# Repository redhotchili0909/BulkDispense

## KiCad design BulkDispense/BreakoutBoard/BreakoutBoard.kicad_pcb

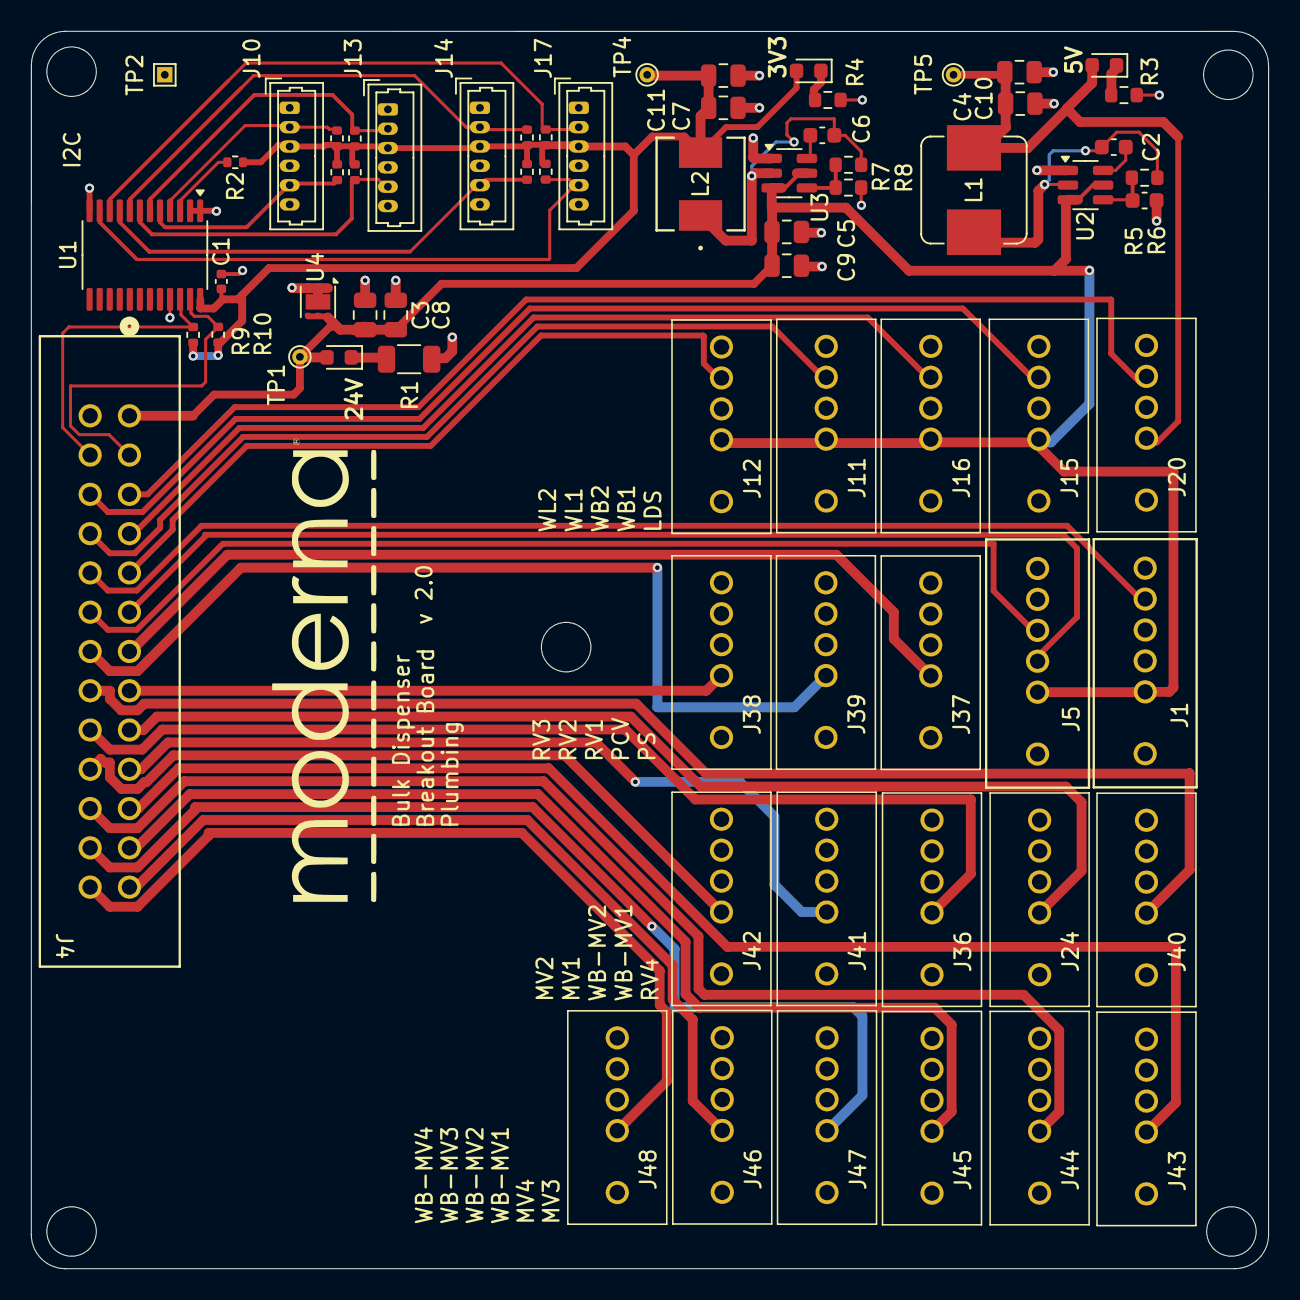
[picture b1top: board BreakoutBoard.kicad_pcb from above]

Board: 2 copper layers, 80.0 x 80.0 mm, 73 parts (0 on the bottom side), 46 nets.

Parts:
C1: 10uF; C_0402_1005Metric
C2, C6: 0.1uF; C_0603_1608Metric
C3, C5, C8, C9: 4.7uF; C_0805_2012Metric
C4, C7, C10, C11: 22uF; C_0805_2012Metric
D1, D3, D4: LED; LED_0603_1608Metric
H1, H2, H3, H4, H5: MountingHole; MountingHole_3.2mm_M3
J1: PS; CONN_37204-62A3-004PL_3MM
J4: Signal; CONN26_D13-ST-BK_SUL
J5: PCV; CONN_37204-62A3-004PL_3MM
J10: FS1; Molex_PicoBlade_53047-0610_1x06_P1.25mm_Vertical
J11: WL1; CONN_37203-62A3-003PL_3MM
J12: WL2; CONN_37203-62A3-003PL_3MM
J13: FS2; Molex_PicoBlade_53047-0610_1x06_P1.25mm_Vertical
J14: FS3; Molex_PicoBlade_53047-0610_1x06_P1.25mm_Vertical
J15: WB1; CONN_37203-62A3-003PL_3MM
J16: WB2; CONN_37203-62A3-003PL_3MM
J17: FS4; Molex_PicoBlade_53047-0610_1x06_P1.25mm_Vertical
J20: LDS; CONN_37203-62A3-003PL_3MM
J24, J45: WB-MV1; CONN_37203-62A3-003PL_3MM
J36, J47: WB-MV2; CONN_37203-62A3-003PL_3MM
J37: RV1; CONN_37203-62A3-003PL_3MM
J38: RV3; CONN_37203-62A3-003PL_3MM
J39: RV2; CONN_37203-62A3-003PL_3MM
J40: RV4; CONN_37203-62A3-003PL_3MM
J41: MV1; CONN_37203-62A3-003PL_3MM
J42: MV2; CONN_37203-62A3-003PL_3MM
J43: MV3; CONN_37203-62A3-003PL_3MM
J44: MV4; CONN_37203-62A3-003PL_3MM
J46: WB-MV3; CONN_37203-62A3-003PL_3MM
J48: WB-MV4; CONN_37203-62A3-003PL_3MM
L1: 6.8uH; L_Bourns_SRP7028A_7.3x6.6mm
L2: 5.6uH; IND_IHLP-2020CZ
R1: 2.2k; R_1206_3216Metric
R2: 10k; R_0402_1005Metric
R3: 330; R_0603_1608Metric
R4: 150; R_0603_1608Metric
R5, R7: 100k; R_0603_1608Metric
R6: 13.7k; C_0603_1608Metric
R8: 22.1k; R_0603_1608Metric
R9, R10, R14, R15, R16, R17, R18, R19, R20, R28: 4.7k; R_0402_1005Metric
TP1, TP4, TP5: TestPoint; TestPoint_THTPad_D1.0mm_Drill0.5mm
TP2: TestPoint; TestPoint_THTPad_1.0x1.0mm_Drill0.5mm
U1: TCA9548APWR; TSSOP-24_4.4x7.8mm_P0.65mm
U2, U3: LMR51430; SOT-23-6
U4: TVS2700DRV; WSON-6-1EP_2x2mm_P0.65mm_EP1x1.6mm

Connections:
+3.3V: C1.1, C7.1, C11.1, D4.2 (A), J10.3, J13.3, J14.3, J17.3, L2.2, R2.1, R9.2, R10.2, R14.2, R15.2, R16.2, R17.2, R18.2, R19.2, R20.2, R28.2, TP4.1, U1.24 (VCC)
+5V: C4.1, C10.1, D3.2 (A), J20.1, L1.2, TP5.1
+24V: C3.1, C5.1, C8.1, C9.1, D1.2 (A), J1.1, J4.1, J5.1, J11.1, J12.1, J15.1, J16.1, TP1.1, U2.3 (VIN), U2.5 (EN), U3.3 (VIN), U3.5 (EN), U4.4 (IN), U4.5 (IN), U4.6 (IN)
/AI4: J4.6, J15.3
/AI5: J4.7, J16.3
/AI6: J4.8, J11.3
/AI7: J4.9, J12.3
/AI12: J1.4, J4.10
/AI13: J4.11, J5.2
/AO0: J4.12, J5.3
/DO0: J4.19, J41.1
/DO1: J4.20, J42.1
/DO2: J4.21, J43.1
/DO3: J4.22, J44.1
/DO4: J4.23, J45.1
/DO5: J4.24, J47.1
/DO6: J4.25, J46.1
/DO7: J4.26, J48.1
/FS1-SCL: J10.5, R14.1, U1.5 (SC0)
/FS1-SDA: J10.2, R15.1, U1.4 (SD0)
/FS2-SCL: J13.5, R16.1, U1.7 (SC1)
/FS2-SDA: J13.2, R17.1, U1.6 (SD1)
/FS3-SCL: J14.5, R18.1, U1.9 (SC2)
/FS3-SDA: J14.2, R19.1, U1.8 (SD2)
/FS4-SCL: J17.5, R20.1, U1.11 (SC3)
/FS4-SDA: J17.2, R28.1, U1.10 (SD3)
/LDS: J4.5, J20.3
/R0_OUT: J4.13, J37.1
/R1_OUT: J4.14, J39.1
/R2_OUT: J4.15, J38.1
/R3_OUT: J4.16, J40.1
/R4_OUT: J4.17, J24.1
/R5_OUT: J4.18, J36.1
/SCL: J4.4, R9.1, U1.22 (SCL)
/SDA: J4.3, R10.1, U1.23 (SDA)
GND: C1.2, C3.2, C4.2, C5.2, C7.2, C8.2, C9.2, C10.2, C11.2, J1.2, J1.3, J4.2, J5.4, J10.1, J10.4, J11.2, J12.2, J13.1, J13.4, J14.1, J14.4, J15.2, J16.2, J17.1, J17.4, J20.2, J24.3, J36.3, J37.3, J38.3, J39.3, J40.3, J41.3, J42.3, J43.3, J44.3, J45.3, J46.3, J47.3, J48.3, R1.2, R3.2, R4.2, R6.2, R8.2, TP2.1, U1.1 (A0), U1.2 (A1), U1.12 (GND), U1.21 (A2), U2.1 (GND), U3.1 (GND), U4.1 (GND), U4.2 (GND), U4.3 (GND), U4.7 (GND)
unnamed: D1.1 (K), R1.1
unnamed: D3.1 (K), R3.1
unnamed: D4.1 (K), R4.1
unnamed: R2.2, U1.3 (~RESET)
unnamed: C2.1, U2.6 (CB)
unnamed: R5.2, R6.1, U2.4 (FB)
unnamed: C2.2, L1.1, R5.1, U2.2 (SW)
unnamed: C6.1, U3.6 (CB)
unnamed: R7.2, R8.1, U3.4 (FB)
unnamed: C6.2, L2.1, R7.1, U3.2 (SW)

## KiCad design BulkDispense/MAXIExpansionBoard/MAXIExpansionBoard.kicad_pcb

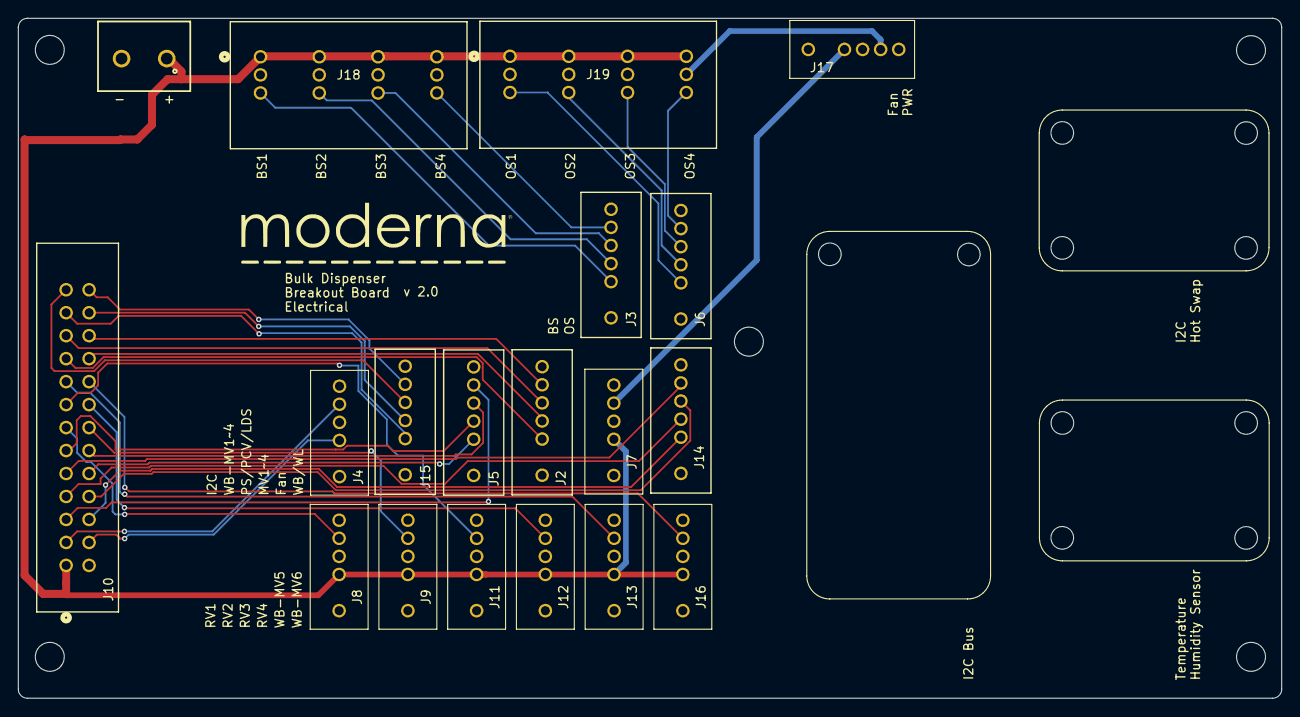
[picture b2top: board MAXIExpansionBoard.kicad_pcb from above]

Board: 2 copper layers, 139.7 x 75.2 mm, 34 parts (0 on the bottom side), 35 nets.

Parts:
H1, H2, H3, H4, H5: MountingHole; MountingHole_3.2mm_M3
H6, H6#2, H7, H7#2, H8, H8#2, H9, H9#2, H10, H11: MountingHole; MountingHole_2.5mm
J1: Screw_Terminal_01x02; 691137710002
J2: MV1~4; CONN_37204-62A3-004PL_3MM
J3: BS1~4; CONN_37204-62A3-004PL_3MM
J4: I2C; CONN_37203-62A3-003PL_3MM
J5: PS/PCV/LDS; CONN_37204-62A3-004PL_3MM
J6: OS1~4; CONN_37204-62A3-004PL_3MM
J7, J9, J11, J12: Fan; CONN_37203-62A3-003PL_3MM
J8: RV1; CONN_37203-62A3-003PL_3MM
J10: Signal; CONN26_D13-ST-BK_SUL
J13: WB-MV5; CONN_37203-62A3-003PL_3MM
J14: WB/WL; CONN_37204-62A3-004PL_3MM
J15: WB-MV1~4; CONN_37204-62A3-004PL_3MM
J16: WB-MV6; CONN_37203-62A3-003PL_3MM
J17: Fan PWR; CONN_37203-62A3-003PL_3MM
J18: BS1~4; CONN_37212-62M3-003PL_3MM
J19: OS1~4; CONN_37212-62M3-003PL_3MM

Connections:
+24V: J1.1, J7.1, J8.1, J9.1, J10.1, J11.1, J12.1, J13.1, J16.1, J18.1, J18.4, J18.7, J18.10, J19.1, J19.4, J19.7, J19.10
/AI0: J3.1, J18.3
/AI1: J3.2, J18.6
/AI2: J3.3, J18.9
/AI3: J3.4, J18.12
/AI4: J10.6, J14.1
/AI5: J10.7, J14.2
/AI6: J10.8, J14.3
/AI7: J10.9, J14.4
/AI12: J5.1, J10.10
/AI13: J5.2, J10.11
/AO0: J5.3, J10.12
/DI0: J6.1, J19.3
/DI1: J6.2, J19.6
/DI2: J6.3, J19.9
/DI3: J6.4, J19.12
/DO0: J2.1, J10.19
/DO1: J2.2, J10.20
/DO2: J2.3, J10.21
/DO3: J2.4, J10.22
/DO4: J10.23, J15.1
/DO5: J10.24, J15.2
/DO6: J10.25, J15.3
/DO7: J10.26, J15.4
/LDS: J5.4, J10.5
/R0_OUT: J8.3, J10.13
/R1_OUT: J9.3, J10.14
/R2_OUT: J10.15, J11.3
/R3_OUT: J10.16, J12.3
/R4_OUT: J10.17, J13.3
/R5_OUT: J10.18, J16.3
/R6_OUT: J7.3, J17.1
/SCL: J4.1, J10.4
/SDA: J4.3, J10.3
GND: J1.2, J10.2, J17.3, J18.2, J18.5, J18.8, J18.11, J19.2, J19.5, J19.8, J19.11

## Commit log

2025-06-06 System + Wiring Diagram
2025-06-09 Most Recent Changes
    Added New Connector Type (3M Mini-Clamp Series)
2025-06-09 Update 3POS Connectors with Mini-Clamp
2025-06-10 First Draft of BreakoutBoard
    - Included MAXI Expansion Board Starter
2025-06-10 Add more documentation + holding mounts
2025-06-12 Finished Up Board + MAXIExpansionBoard
2025-06-13 Add STEP files
2025-06-13 Add schematic PDF
2025-06-13 Design Overhaul
2025-06-16 Add latest design
2025-06-17 Update Lynx Actuator Wiring Diagram
2025-06-18 Update PCB + Add Lynx Wiring Diagram
2025-06-18 Visual Edits
2025-06-20 Edit BOM
    Format BOM to PCBWay's Request
2025-06-30 Add updated layout
2025-08-01 Add PCB Revisions
2025-08-04 PCB Changes
2025-08-05 Add New Design
2025-08-05 Start PCB Routing
2025-08-07 Start I2C Layout
2025-08-07 Finalized Draft - BreakoutBoard
2025-08-08 Final Design Changes for Both Boards
2025-08-08 Final Update
